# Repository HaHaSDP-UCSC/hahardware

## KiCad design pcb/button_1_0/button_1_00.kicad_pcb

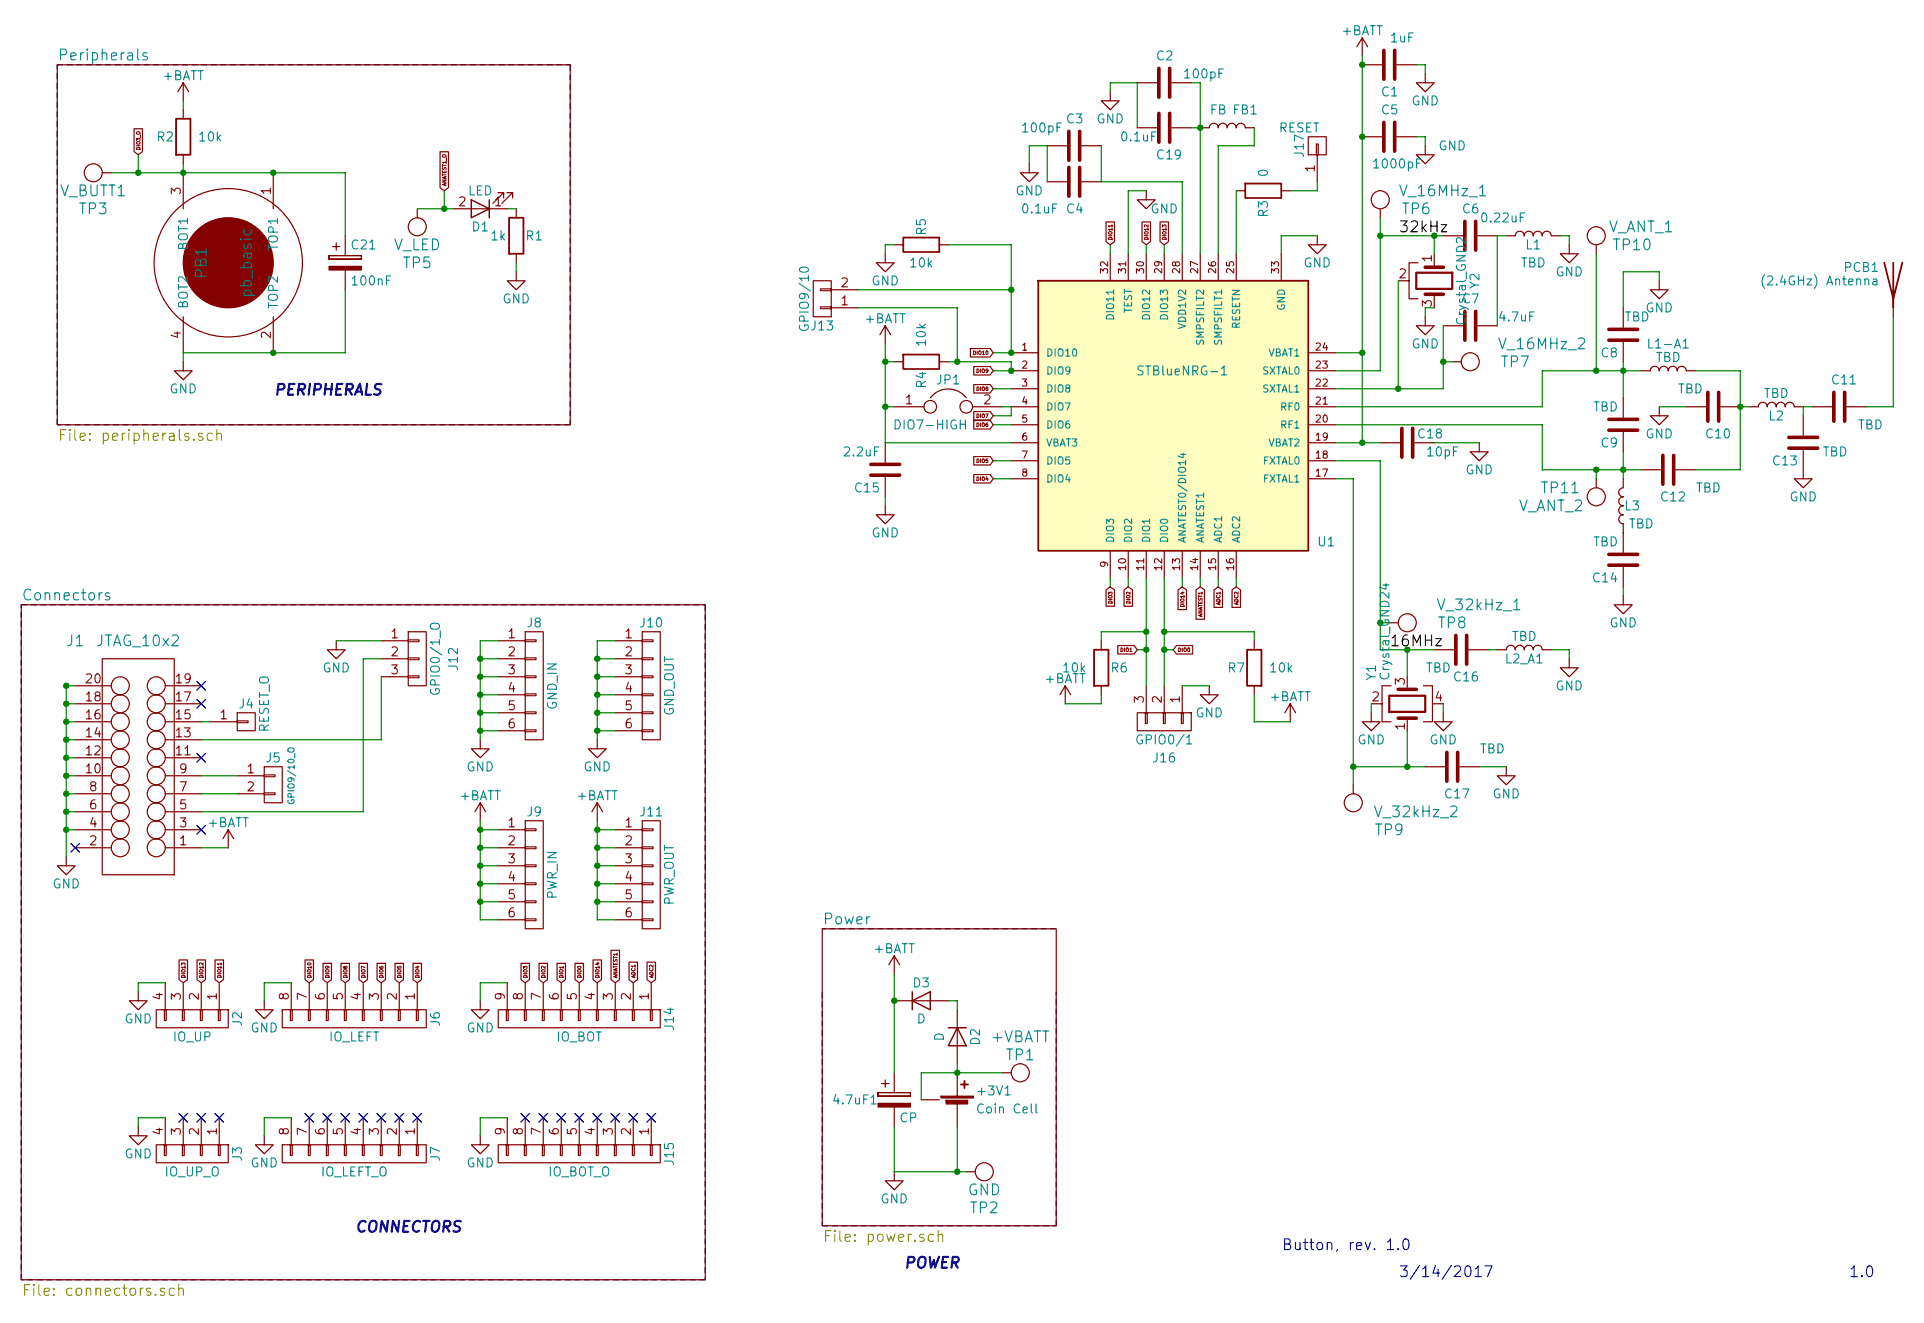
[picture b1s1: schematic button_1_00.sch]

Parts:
4.7uF1: CP; C_0603
+3V1: Coin Cell; SMD_CoinCell
C1: 1uF; C_0402
C2, C3: 100pF; C_0402
C4, C19: 0.1uF; C_0402
C5: 1000pF; C_0402
C6: 0.22uF; C_0402
C7: 4.7uF; C_0402
C8, C9, C10, C11, C12, C13, C14, C16, C17: TBD; C_0402
C15: 2.2uF; C_0402
C18: 10pF; C_0402
C21: 100nF; C_0603_HandSoldering
D1: LED; LED_0603
D2, D3: D; D_0603
FB1: FB; Neosid_Inductor_SM0603CG
J1: JTAG_10x2; Multicomp_MC9A12-2034_2x10x2.54mm_Straight
J2: IO_UP; Pin_Header_Straight_1x04_Pitch2.54mm
J3: IO_UP_O; Pin_Header_Straight_1x04_Pitch2.54mm
J4: RESET_O; Pin_Header_Straight_1x01_Pitch2.54mm
J5: GPIO9/10_O; Pin_Header_Straight_1x02_Pitch2.54mm
J6: IO_LEFT; Pin_Header_Straight_1x08_Pitch2.54mm
J7: IO_LEFT_O; Pin_Header_Straight_1x08_Pitch2.54mm
J8: GND_IN; Pin_Header_Straight_1x06_Pitch1.27mm
J9: PWR_IN; Pin_Header_Straight_1x06_Pitch1.27mm
J10: GND_OUT; Pin_Header_Straight_1x06_Pitch1.27mm
J11: PWR_OUT; Pin_Header_Straight_1x06_Pitch1.27mm
J12: GPIO0/1_O; Pin_Header_Straight_1x03_Pitch2.54mm
J13: GPIO9/10; Pin_Header_Straight_1x02_Pitch2.54mm
J14: IO_BOT; Pin_Header_Straight_1x09_Pitch2.54mm
J15: IO_BOT_O; Pin_Header_Straight_1x09_Pitch2.54mm
J16: GPIO0/1; Pin_Header_Straight_1x03_Pitch2.54mm
J17: RESET; Pin_Header_Straight_1x01_Pitch2.54mm
JP1: DIO7-HIGH; Pin_Header_Straight_1x02_Pitch2.54mm
L1, L1-A1, L2, L2_A1, L3: TBD; Neosid_Inductor_SM0603CG
PB1: pb_basic
PCB1: (2.4GHz) Antenna; Molex_SMA_Jack_Edge_Mount
R1: 1k; R_0603
R2, R4, R5, R6, R7: 10k; R_0603
R3: 0; R_0603
TP1: +VBATT; TP_gen
TP2: GND; TP_gen
TP3: V_BUTT1; TP_gen
TP5: V_LED; TP_gen
TP6: V_16MHz_1; TP_gen
TP7: V_16MHz_2; TP_gen
TP8: V_32kHz_1; TP_gen
TP9: V_32kHz_2; TP_gen
TP10: V_ANT_1; TP_gen
TP11: V_ANT_2; TP_gen
U1: STBlueNRG-1; QFN-32-1EP_5x5mm
Y1: Crystal_GND24; Crystal_SMD_2520-4pin_2.5x2.0mm
Y2: Crystal_GND2; Crystal_C26-LF_d2.1mm_l6.5mm_Horizontal_1EP_style1

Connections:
+BATT: 4.7uF1.1, C1.2, C5.2, C15.2, C18.2, D3.1 (K), J1.1 (U_TG), J9.1, J9.2, J9.3, J9.4, J9.5, J9.6, J11.1, J11.2, J11.3, J11.4, J11.5, J11.6, JP1.1, R2.1, R4.2, R6.2, R7.2, U1.6 (VBAT3), U1.19 (VBAT2), U1.24 (VBAT1); also elsewhere on the board
/16MHz: C16.2, TP8.1, U1.18 (FXTAL0), Y1.3
/32kHz: C6.2, TP6.1, U1.23 (SXTAL0), Y2.1
ADC1: J14.2, U1.15 (ADC1)
ADC2: J14.1, U1.16 (ADC2)
ANATEST1: J14.3, U1.14 (ANATEST1)
ANATEST1_O: D1.2 (A), TP5.1
DIO0: J14.5, J16.2, R7.1, U1.12 (DIO0)
DIO1: J14.6, J16.3, R6.1, U1.11 (DIO1)
DIO2: J14.7, U1.10 (DIO2)
DIO3: J14.8, U1.9 (DIO3)
DIO3_O: C21.1, PB1.1 (TOP1), PB1.3 (BOT1), R2.2, TP3.1
DIO4: J6.1, U1.8 (DIO4)
DIO5: J6.2, U1.7 (DIO5)
DIO6: J6.3, U1.5 (DIO6)
DIO7: J6.4, JP1.2, U1.4 (DIO7)
DIO8: J6.5, U1.3 (DIO8)
DIO9: J6.6, J13.1, R4.1, U1.2 (DIO9)
DIO10: J6.7, J13.2, R5.2, U1.1 (DIO10)
DIO11: J2.1, U1.32 (DIO11)
DIO12: J2.2, U1.30 (DIO12)
DIO13: J2.3, U1.29 (DIO13)
DIO14: J14.4, U1.13 (ANATEST0/DIO14)
GND: 4.7uF1.2, +3V1.1 (-), C1.1, C2.2, C3.2, C4.2, C5.1, C8.2, C10.2, C13.1, C14.1, C15.1, C17.1, C18.1, C19.2, C21.2, J1.4 (GND), J1.6 (GND), J1.8 (GND), J1.10 (GND), J1.12 (GND), J1.14 (GND), J1.16 (GND), J1.18 (GND), J1.20 (GND), J2.4, J3.4, J6.8, J7.8, J8.1, J8.2, J8.3, J8.4, J8.5, J8.6, J10.1, J10.2, J10.3, J10.4, J10.5, J10.6, J12.1, J14.9, J15.9, J16.1, L1.2, L2_A1.2, PB1.2 (TOP2), PB1.4 (BOT2), R1.2, R5.1, TP2.1, U1.31 (TEST), U1.33 (GND), Y1.2, Y1.4, Y2.3; also elsewhere on the board
unnamed: +3V1.2 (+), +3V1.3 (+), D2.2 (A), TP1.1
unnamed: C3.1, C4.1, U1.28 (VDD1V2)
unnamed: C6.1, C7.1, L1.1
unnamed: C7.2, TP7.1, U1.22 (SXTAL1), Y2.2
unnamed: C8.1, C9.2, L1-A1.1, TP10.1, U1.21 (RF0)
unnamed: C10.1, C12.1, L1-A1.2, L2.1
unnamed: C11.1, PCB1.1
unnamed: C11.2, C13.2, L2.2
unnamed: C9.1, C12.2, L3.2, TP11.1, U1.20 (RF1)
unnamed: C14.2, L3.1
unnamed: C16.1, L2_A1.1
unnamed: C17.2, TP9.1, U1.17 (FXTAL1), Y1.1
unnamed 36: C2.1, C19.1, FB1.1, U1.27 (SMPSFILT2); also elsewhere on the board
unnamed: D1.1 (K), R1.1
unnamed: D2.1 (K), D3.2 (A)
unnamed: FB1.2, U1.26 (SMPSFILT1)
unnamed: J1.5 (TDI), J12.2
unnamed: J1.7 (TMS/SWDIO), J5.2
unnamed: J1.9 (TCK/SWCLK), J5.1
unnamed: J1.13 (TDO/SWO), J12.3
unnamed: J1.15 (nSRST), J4.1
unnamed: J17.1, R3.1
unnamed: R3.2, U1.25 (RESETN)

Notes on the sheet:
Button, rev. 1.0
1.0
3/14/2017
POWER
CONNECTORS
PERIPHERALS

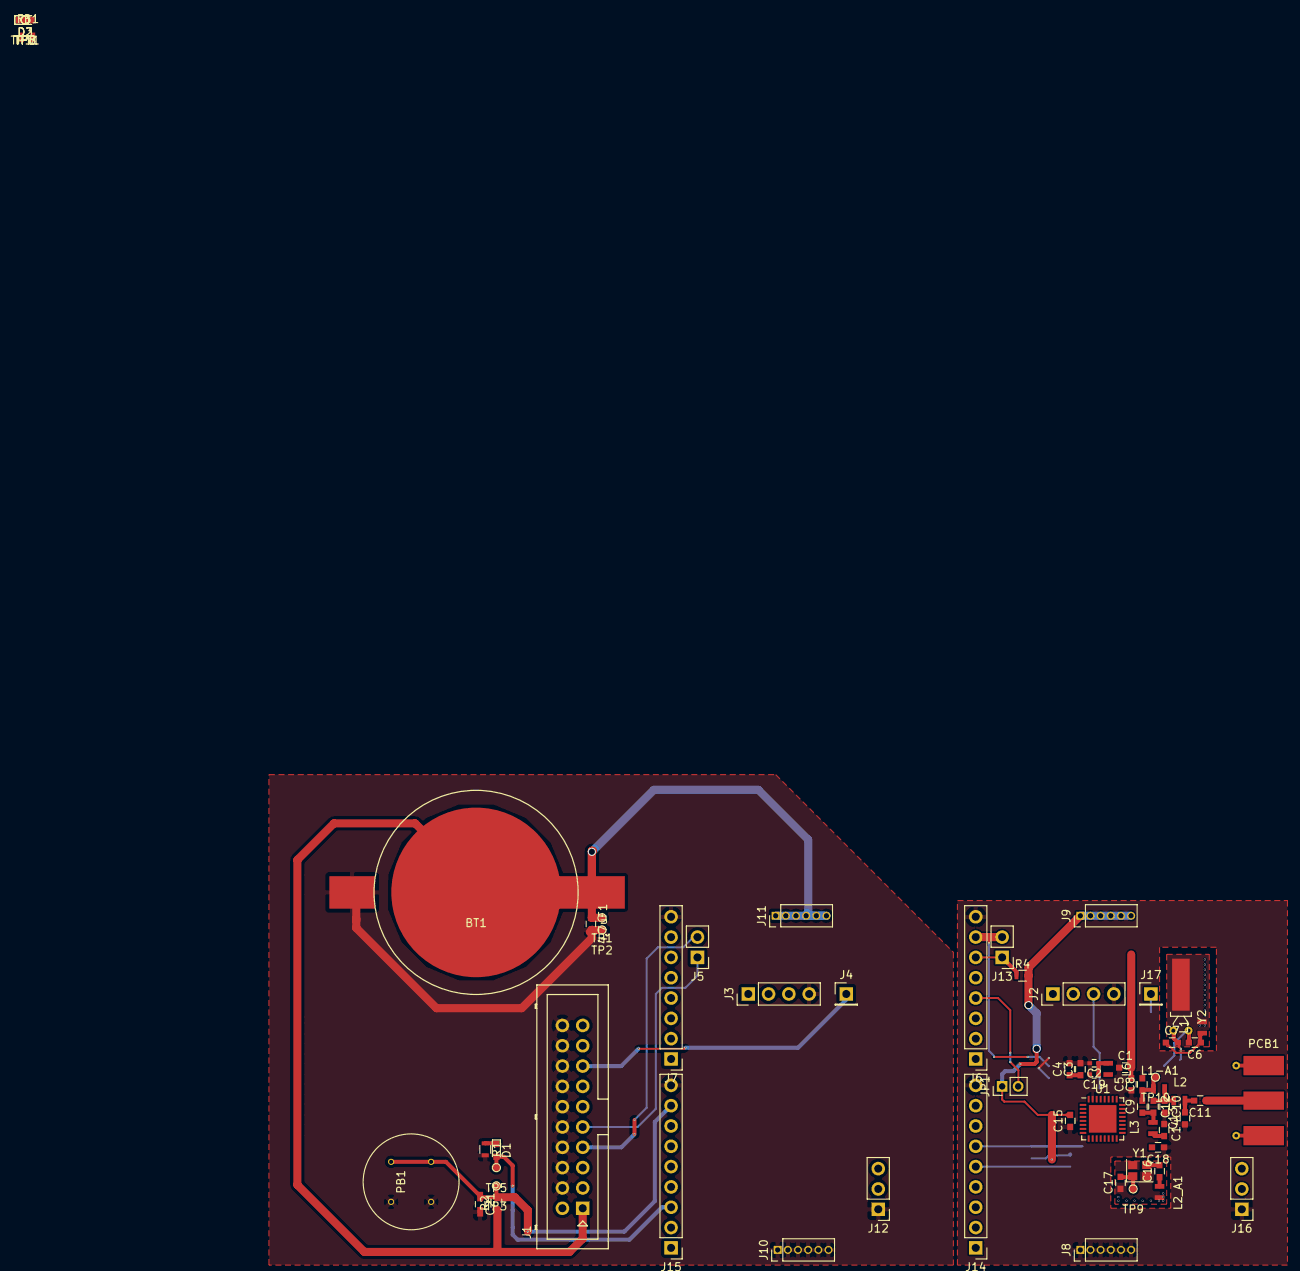
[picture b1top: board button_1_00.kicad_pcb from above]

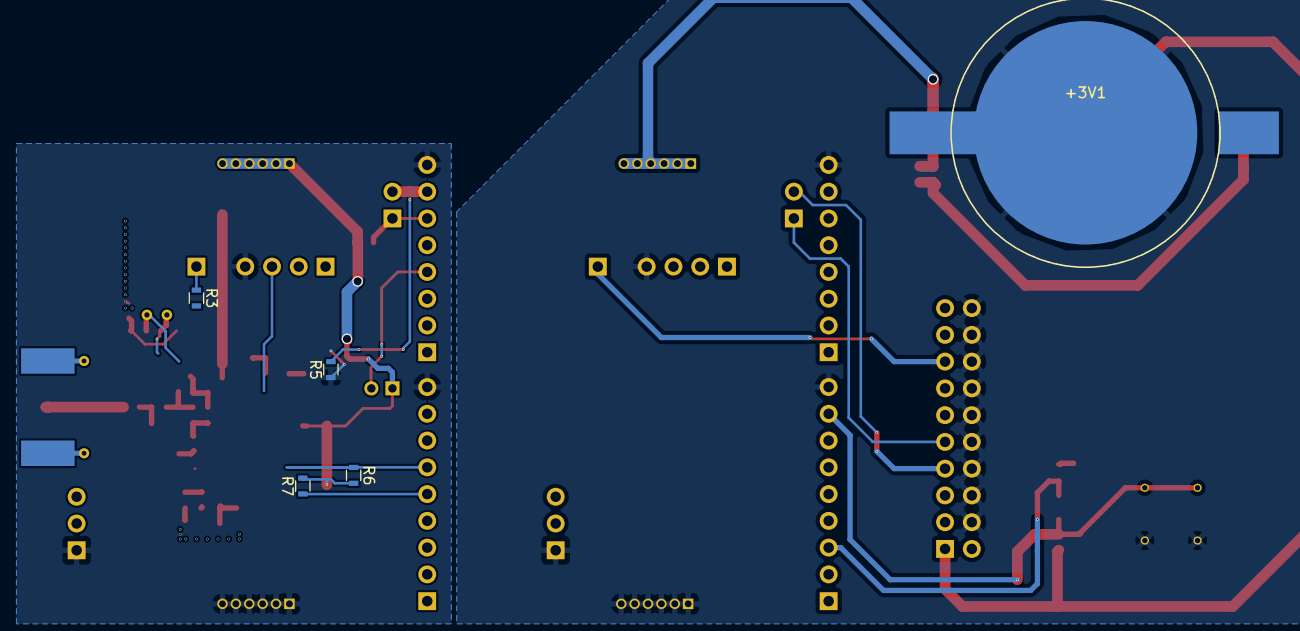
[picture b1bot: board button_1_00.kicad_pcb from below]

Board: 2 copper layers, 73 parts (5 on the bottom side), 47 nets.

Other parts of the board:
BT1: Coin Cell; SMD_CoinCell
L6: L; Neosid_Inductor_SM0603CG

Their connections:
+BATT: BT1.2, BT1.3; also elsewhere on the board
GND: BT1.1; also elsewhere on the board
unnamed 36: L6.1; also elsewhere on the board

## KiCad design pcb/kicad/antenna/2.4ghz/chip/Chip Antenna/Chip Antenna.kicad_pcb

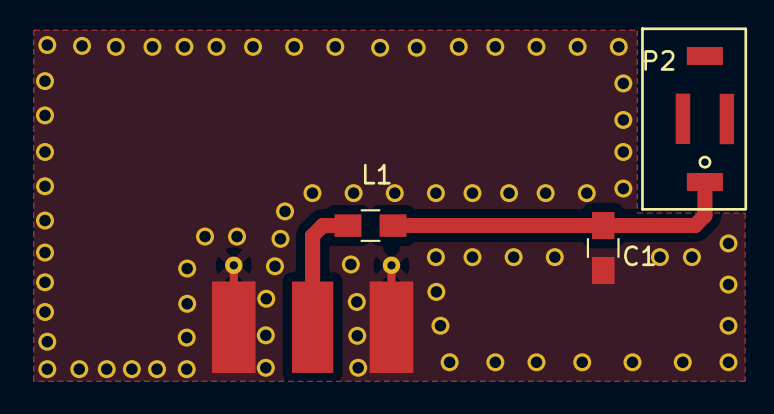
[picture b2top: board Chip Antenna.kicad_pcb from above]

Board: 2 copper layers, 4 parts (0 on the bottom side), 3 nets.

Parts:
C1: 1 pF; C_0805_HandSoldering
L1: 4.7 nH; C_0805_HandSoldering
P1: CONN_01X02; Molex_SMA_Jack_Edge_Mount
P2: CONN_01X02; ChipAntenna

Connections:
GND: C1.2, P1.2
unnamed: C1.1, L1.1, P2.1
unnamed: L1.2, P1.1

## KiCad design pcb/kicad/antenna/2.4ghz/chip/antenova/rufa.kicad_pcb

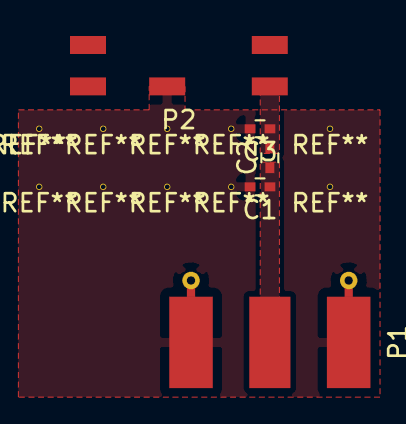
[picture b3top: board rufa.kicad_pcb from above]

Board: 2 copper layers, 5 parts (0 on the bottom side), 3 nets, no tracks yet.

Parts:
C1, C2, C3: C; C_0402
P1: CONN_01X02; Molex_SMA_Jack_Edge_Mount
P2: CONN_01X03; Antenova_Rufa_A5887

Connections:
GND: C1.2, C3.2, P1.2, P2.3
unnamed: C1.1, C2.1, P1.1
unnamed: C2.2, C3.1, P2.1
